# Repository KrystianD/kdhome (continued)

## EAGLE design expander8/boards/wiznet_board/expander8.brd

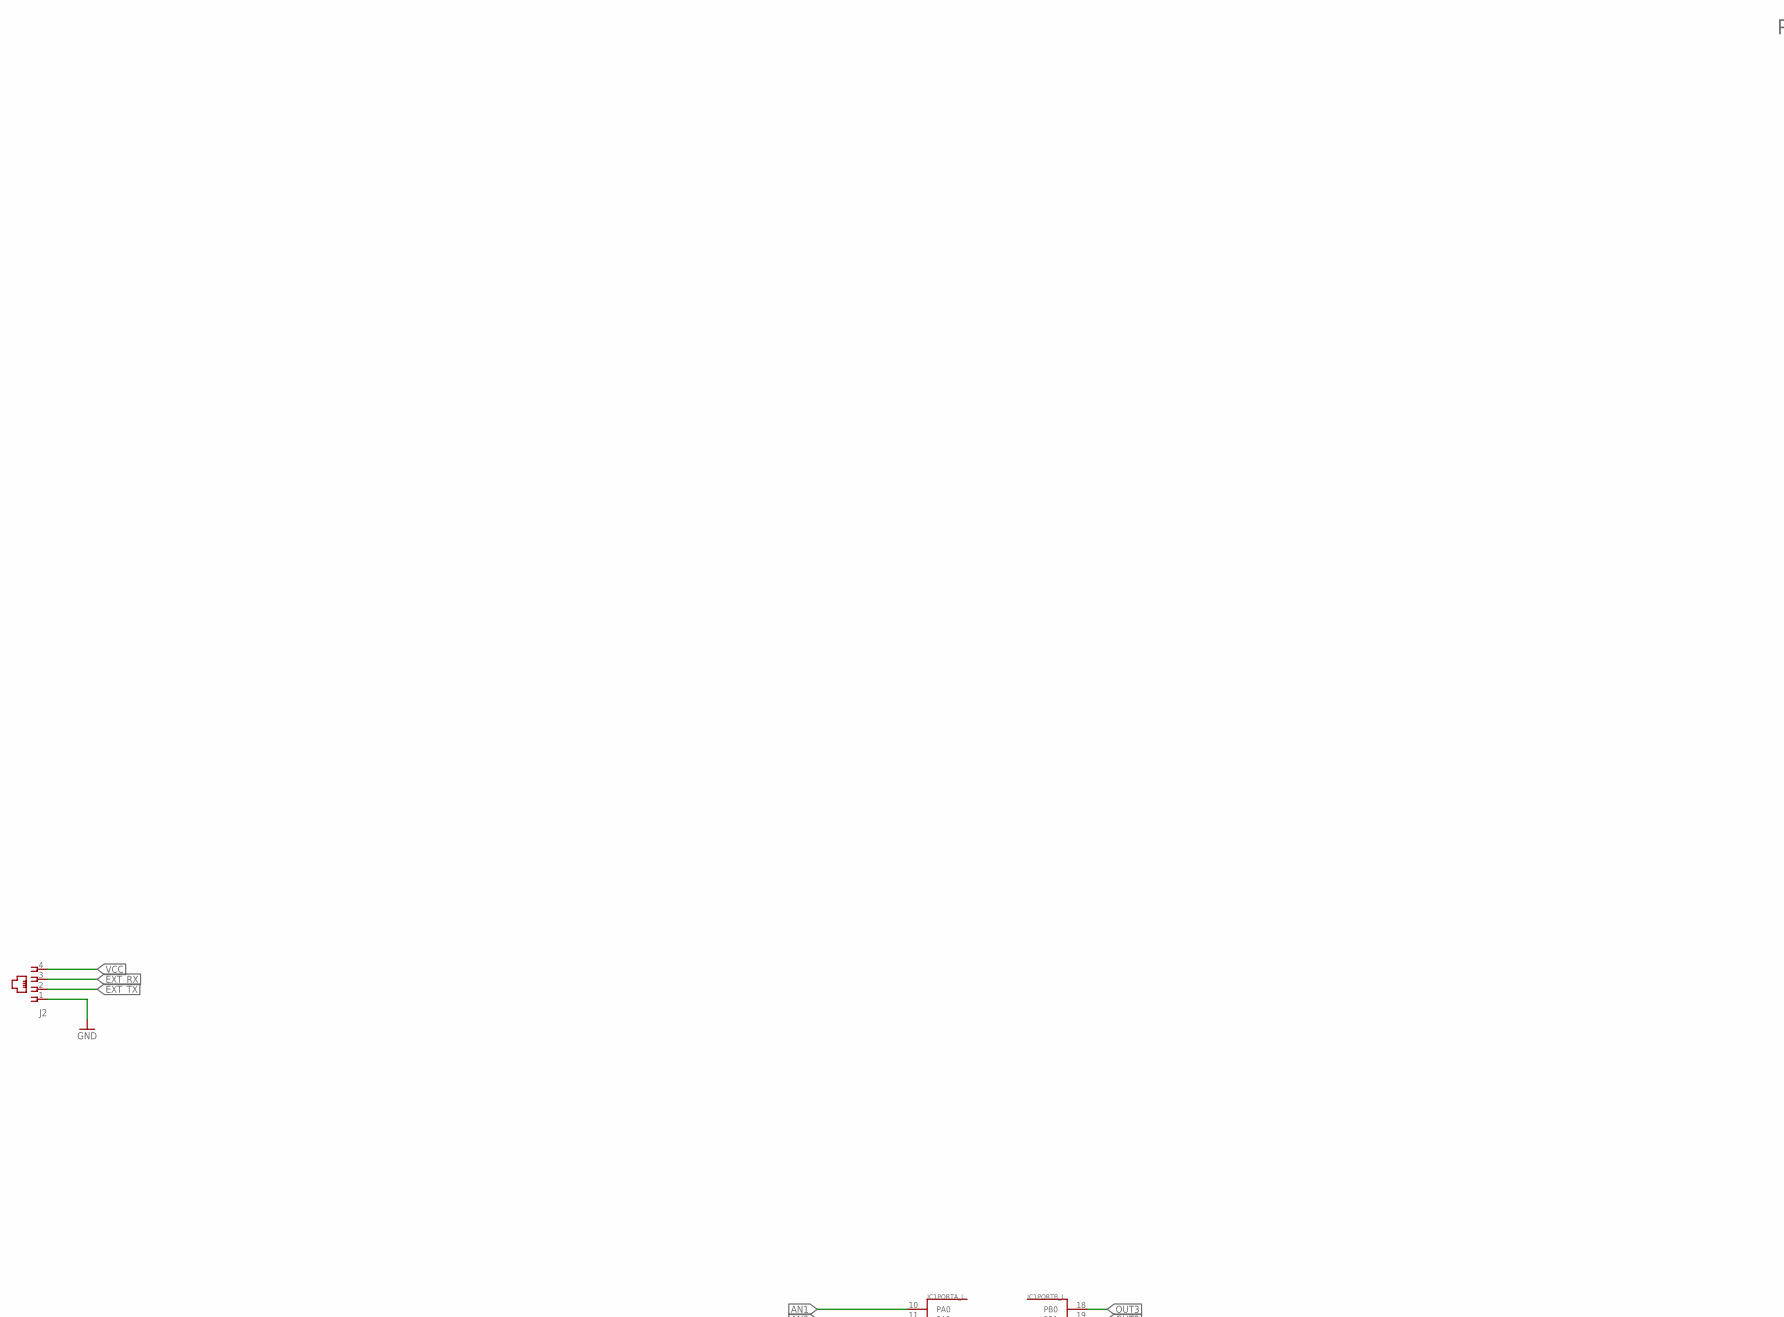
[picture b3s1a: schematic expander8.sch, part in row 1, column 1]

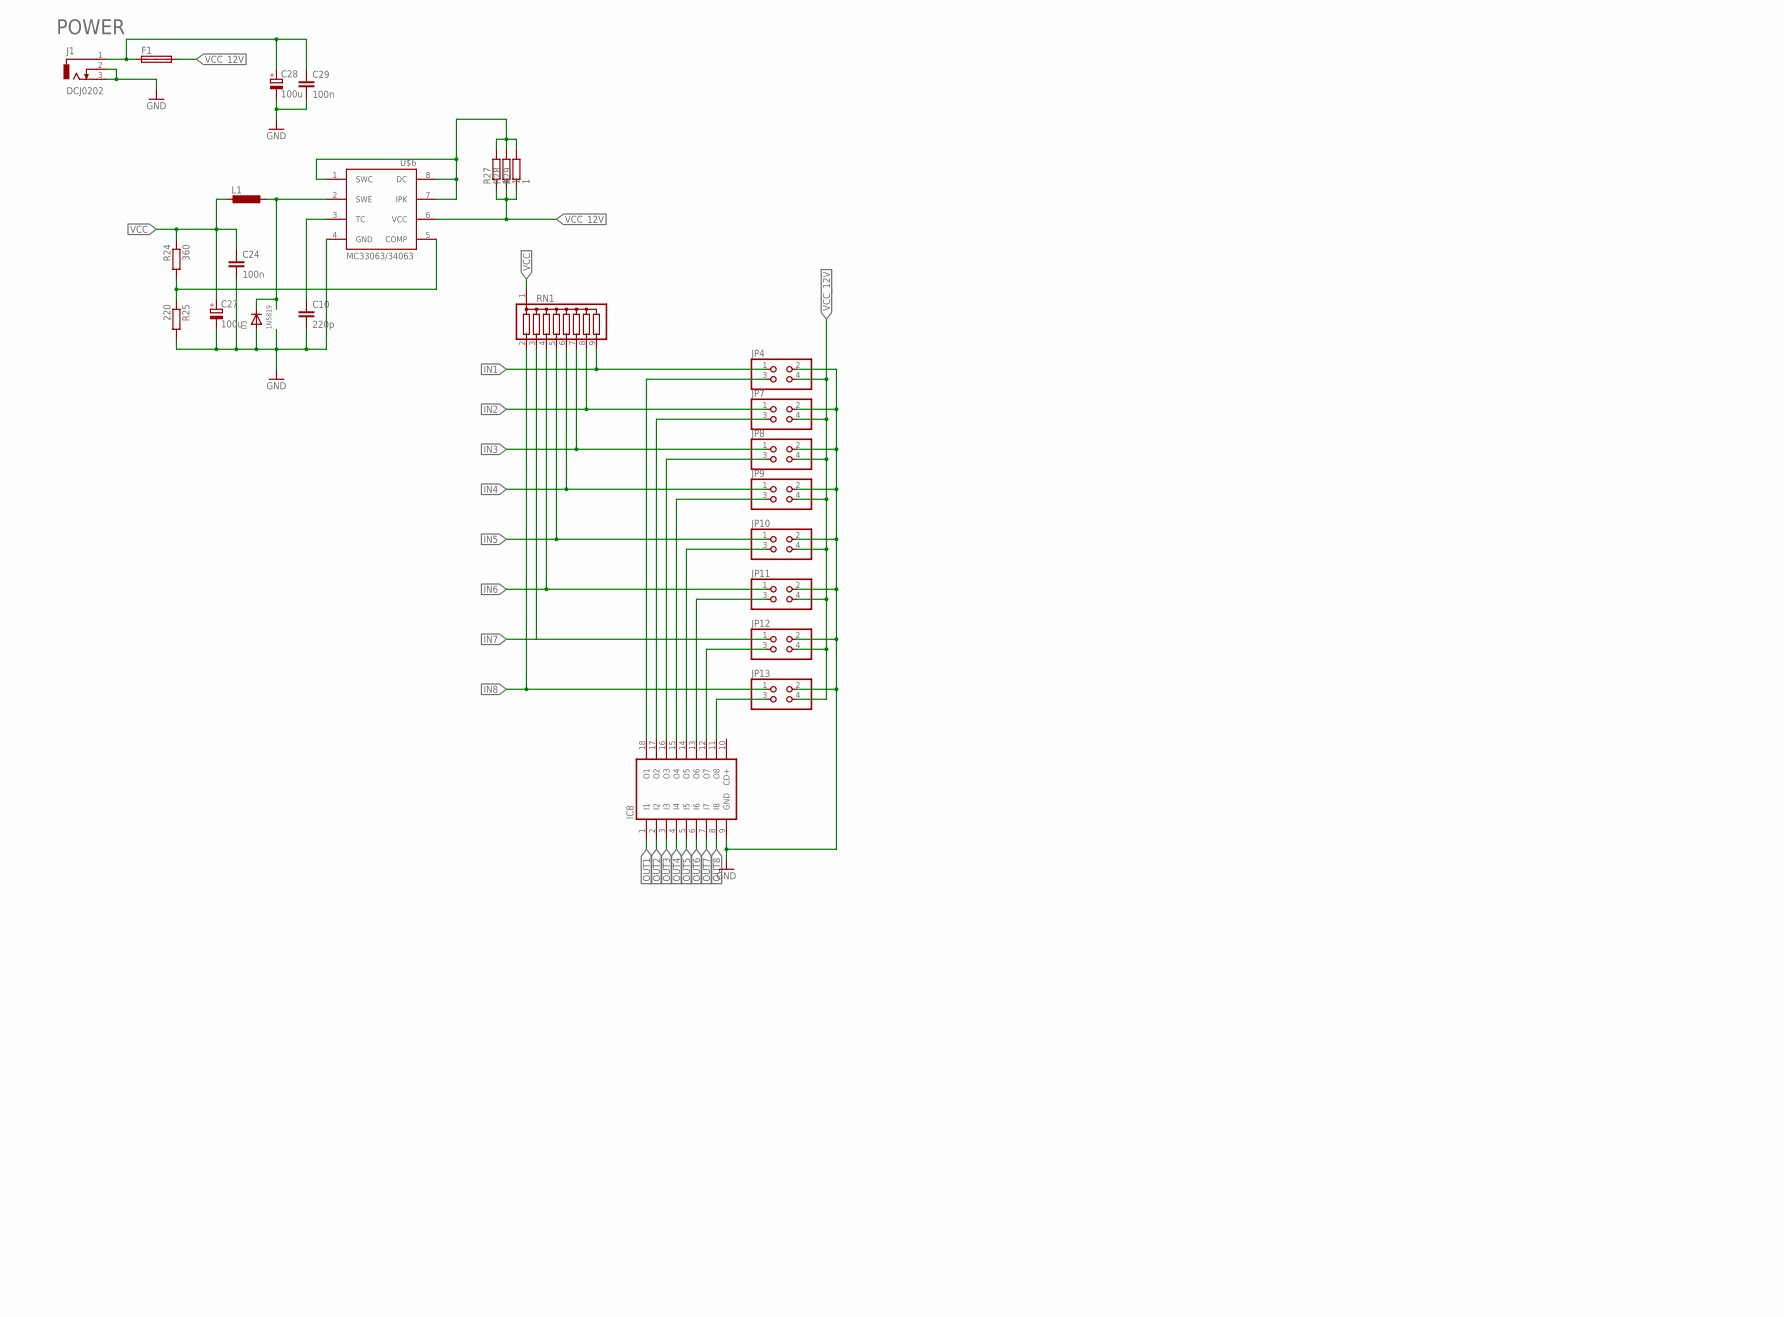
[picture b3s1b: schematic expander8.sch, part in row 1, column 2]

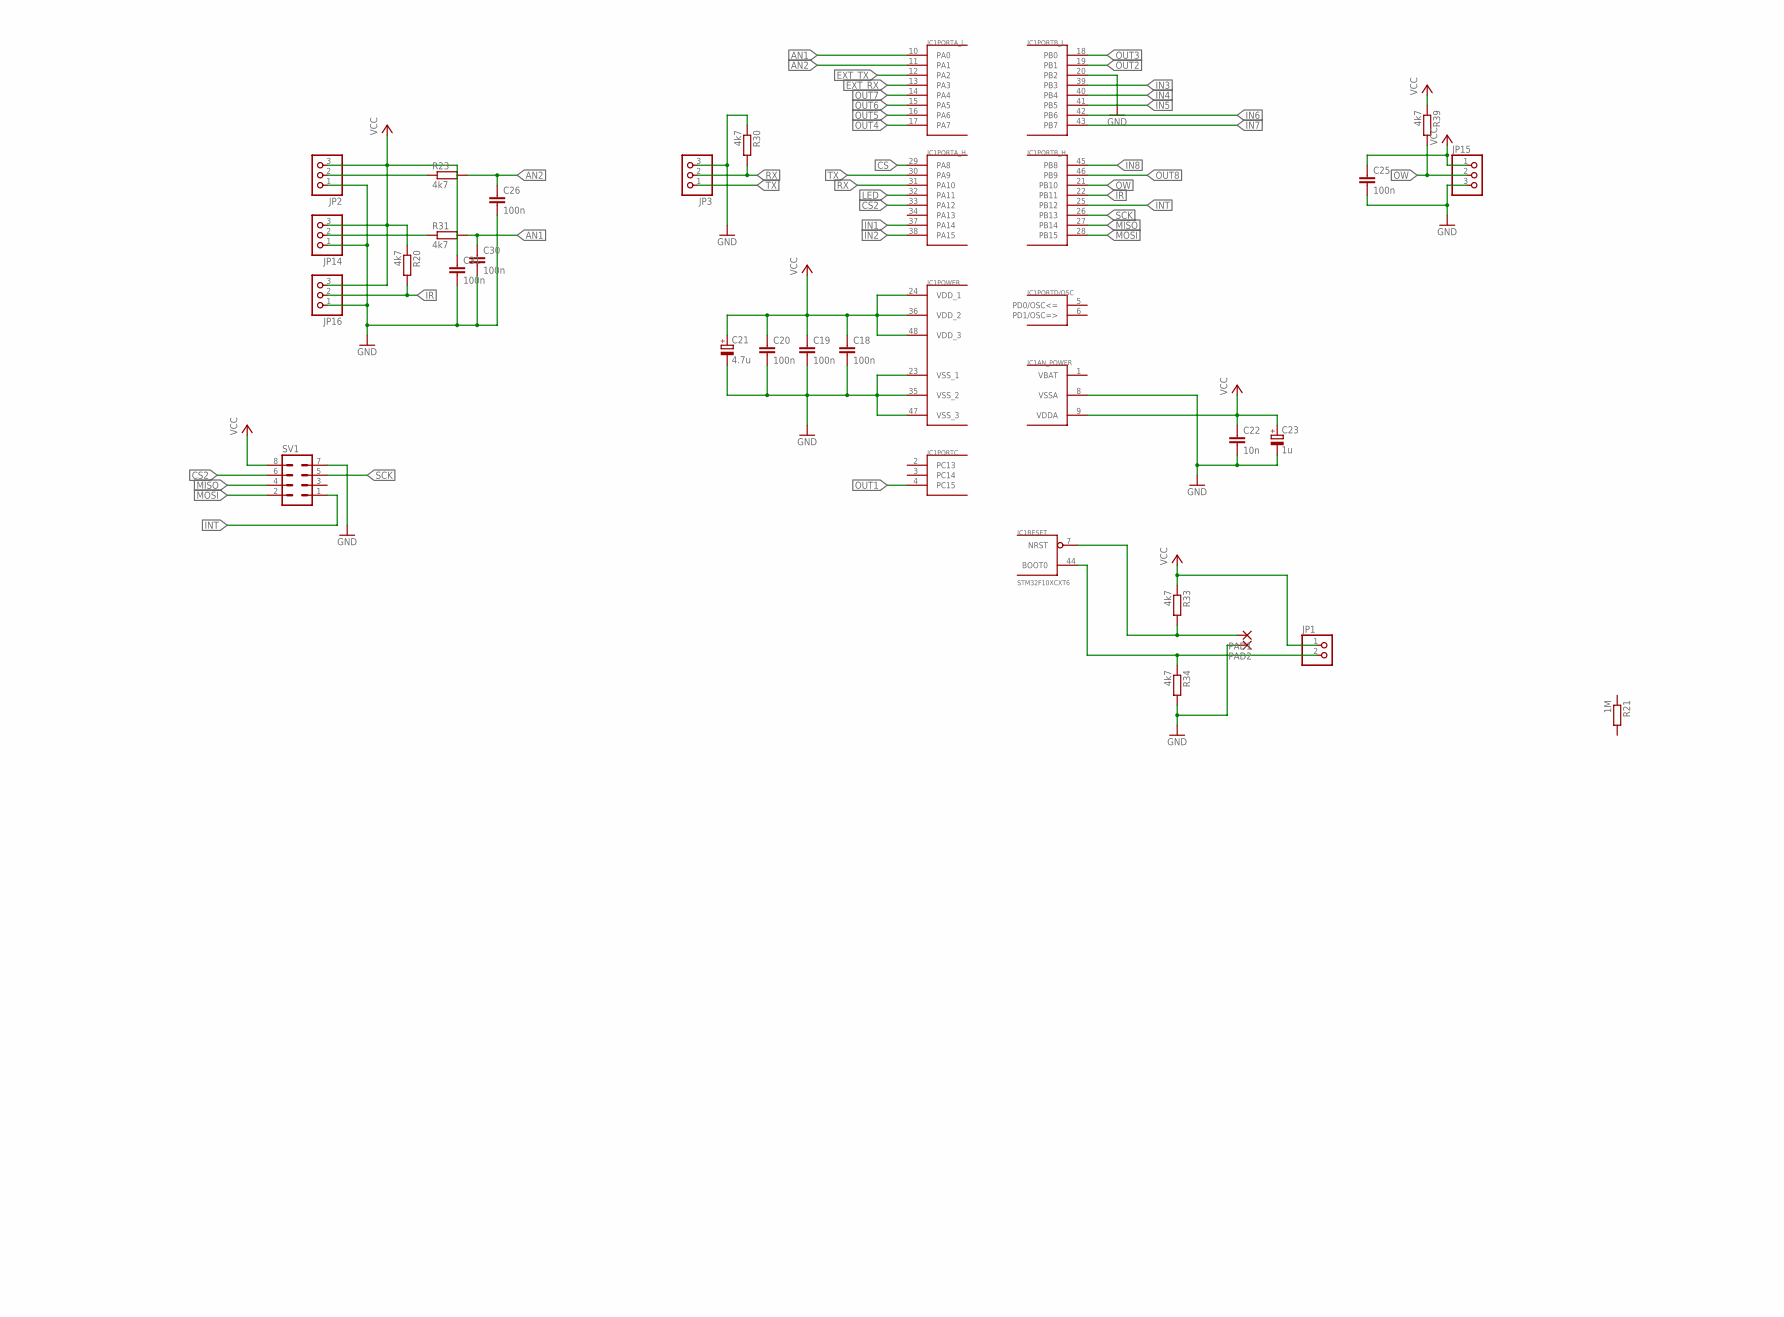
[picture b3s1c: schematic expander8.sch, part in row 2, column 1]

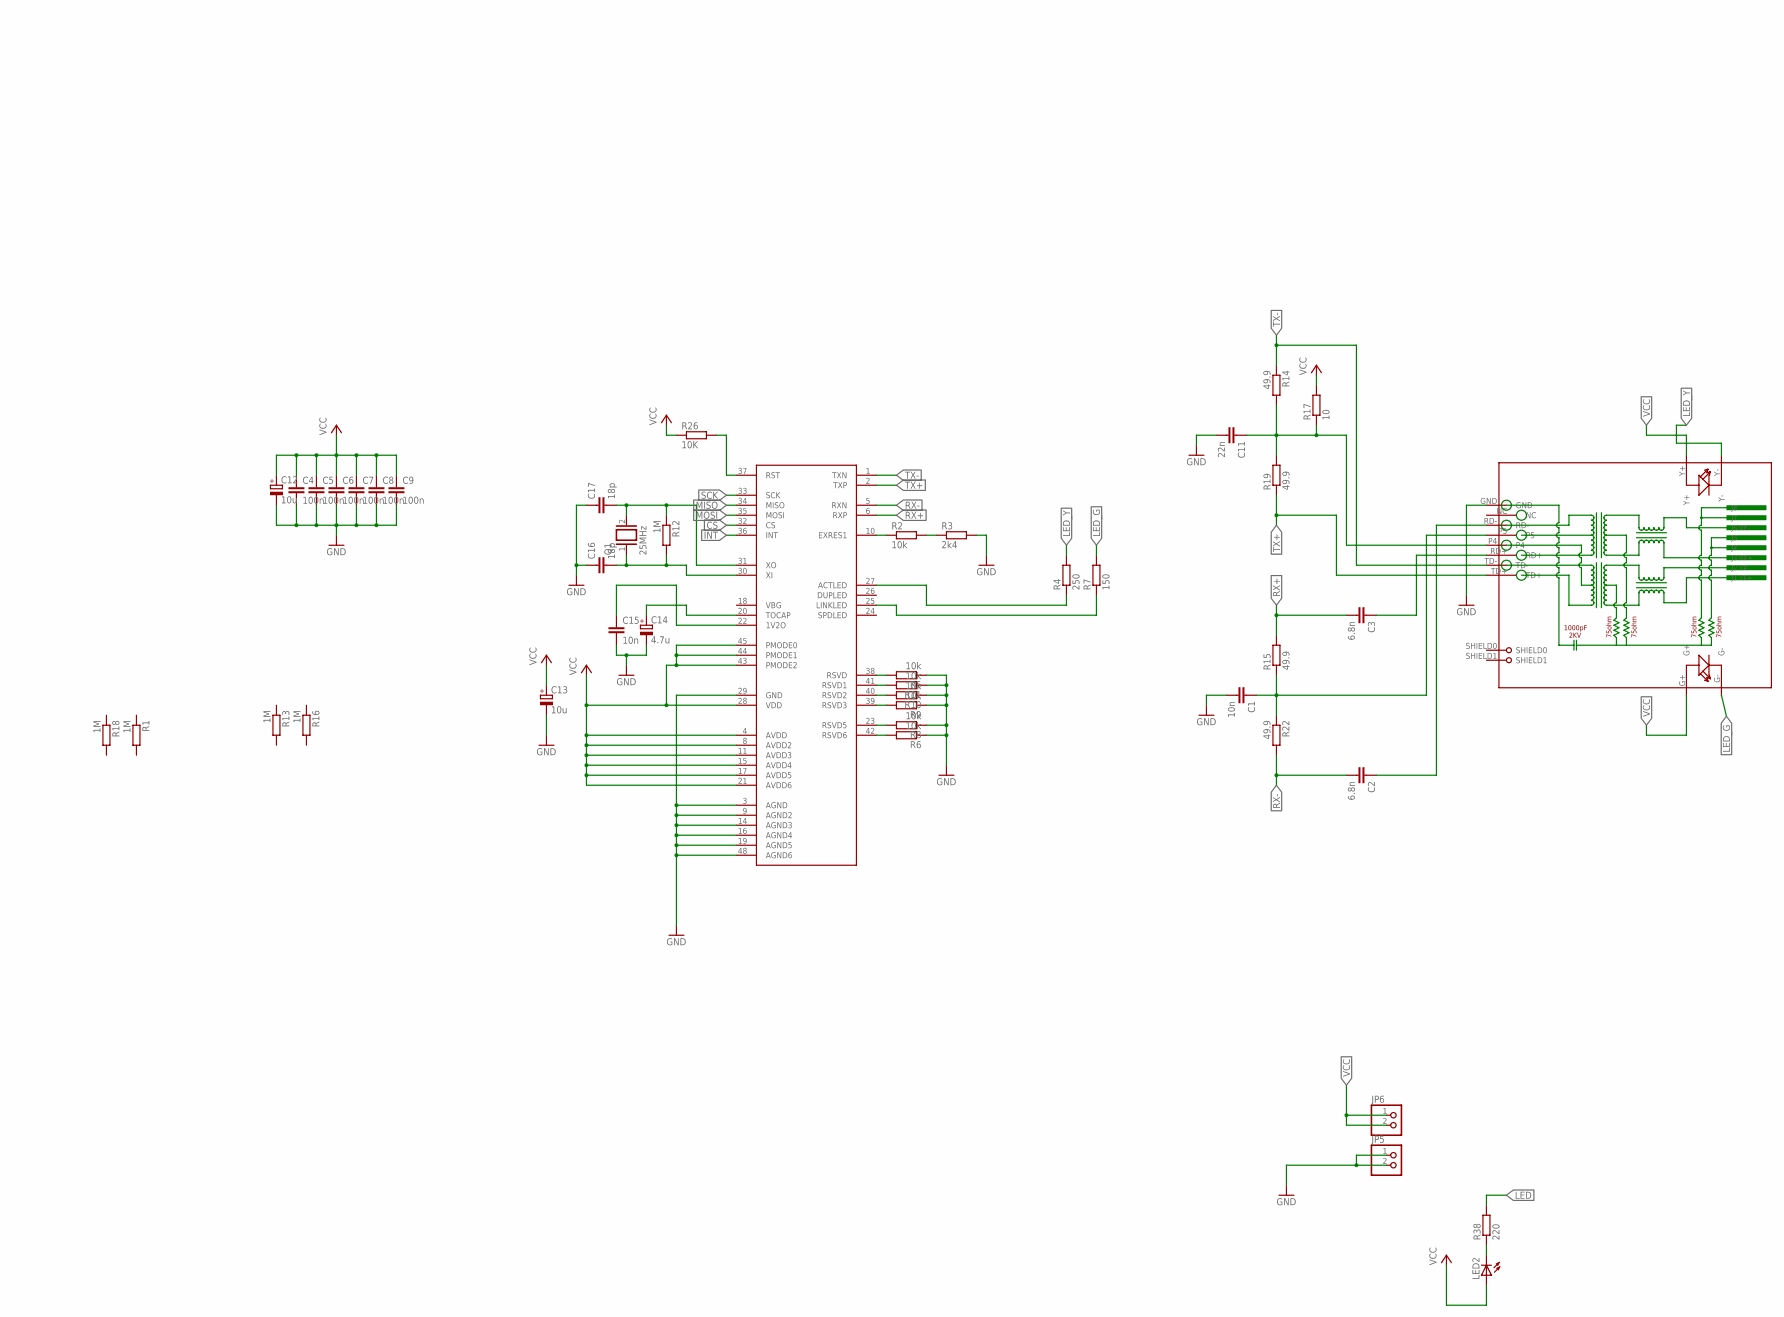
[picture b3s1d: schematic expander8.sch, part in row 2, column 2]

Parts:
C1, C22: 10n; C0805
C2, C3: 6.8n; C0805
C4, C5, C6, C7, C8, C9, C18, C19, C20, C24, C26, C29, C31: 100n; C0805
C10: 220p; C0805
C11: 22n; C0805
C12, C13: 10u; E2,5-5
C14, C21: 4.7u; E2,5-5
C15: 10n; C1206
C16, C17: 18p; C0805
C23: 1u; E2,5-5
C25, C30: 100n; C1206
C27, C28: 100u; E2,5-7
D3: 1N5819; SMADIODE
F1: SHK20L
IC1: STM32F10XCXT6; TQFP48
IC8: ULN2803AD; SO18W
J1: DCJ0202
J2: 520250-2
JP1, JP5, JP6: PINHD-1X2; 1X02
JP2, JP3, JP14, JP15, JP16: PINHD-1X3; 1X03
JP4, JP7, JP8, JP9, JP10, JP11, JP12, JP13: PINHD-2X2/90; 2X02/90
L1: L-EU0207/2V; 0207/2V
LED2: LEDCHIPLED_0805; CHIPLED_0805
PAD1, PAD2: SMD2; SMD1,27-2,54
Q1: 25MHz; QS
R1, R13, R16, R18, R21: 1M; R1206
R2, R8: 10k; R0805
R3: 2k4; R0805
R4: 250; R1206
R5, R6, R9, R10, R11: 10k; R0603
R7: 150; R1206
R12: 1M; R0805
R14, R22: 49.9; R0805
R15, R19: 49.9; R1206
R17: 10; R0805
R20, R23, R31, R33, R39: 4k7; R0805
R24: 360; M1206
R25: 220; M1206
R26: 10K; R0805
R27, R28, R29: 1; R1206
R30, R34: 4k7; R1206
R38: 220; R0805
RJ1: HR911105A
RN1: G08R; SIL9
SV1: MA04-2
U$1: W5500; TQFP48
U$6: MC33063/MC34063D; SO08

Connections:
AN1: C30.1, IC1.10 (PA0), R31.2
AN2: C26.1, IC1.11 (PA1), R23.2
COMP: R24.2, R25.1, U$6.5 (COMP)
CS: IC1.29 (PA8), U$1.32 (CS)
CS2: IC1.33 (PA12), SV1.6
EXT_RX: IC1.13 (PA3), J2.3
EXT_TX: IC1.12 (PA2), J2.2
GND: C1.2, C4.2, C5.2, C6.2, C7.2, C8.2, C9.2, C10.2, C11.2, C12.-, C13.-, C14.-, C15.2, C16.1, C17.1, C18.2, C19.2, C20.2, C21.-, C22.2, C23.-, C24.2, C25.2, C26.2, C27.-, C28.-, C29.2, C30.2, C31.2, D3.A, IC1.8 (VSSA), IC1.20 (PB2), IC1.23 (VSS_1), IC1.35 (VSS_2), IC1.47 (VSS_3), IC8.9 (GND), J1.2, J1.3, J2.1, JP2.1, JP3.3, JP4.2, JP5.1, JP5.2, JP7.2, JP8.2, JP9.2, JP10.2, JP11.2, JP12.2, JP13.2, JP14.1, JP15.3, JP16.1, PAD2.1, R3.2, R5.1, R6.1, R8.1, R9.1, R10.1, R11.1, R25.2, R30.1, R34.2, RJ1.GND, SV1.7, U$1.3 (AGND), U$1.9 (AGND2), U$1.14 (AGND3), U$1.16 (AGND4), U$1.19 (AGND5), U$1.29 (GND), U$1.48 (AGND6), U$6.4 (GND)
IN1: IC1.37 (PA14), JP4.1, RN1.9
IN2: IC1.38 (PA15), JP7.1, RN1.8
IN3: IC1.39 (PB3), JP8.1, RN1.7
IN4: IC1.40 (PB4), JP9.1, RN1.6
IN5: IC1.41 (PB5), JP10.1, RN1.5
IN6: IC1.42 (PB6), JP11.1, RN1.4
IN7: IC1.43 (PB7), JP12.1, RN1.3
IN8: IC1.45 (PB8), JP13.1, RN1.2
INT: IC1.25 (PB12), SV1.1, U$1.36 (INT)
IPK: R27.2, R28.2, R29.2, U$6.1 (SWC), U$6.7 (IPK), U$6.8 (DC)
IR: IC1.22 (PB11), JP16.2, R20.2
LED: IC1.32 (PA11), R38.2
LED_G: R7.2, RJ1.G-
LED_Y: R4.2, RJ1.Y-
MISO: IC1.27 (PB14), SV1.4, U$1.34 (MISO)
MOSI: IC1.28 (PB15), SV1.2, U$1.35 (MOSI)
unnamed: C3.1, RJ1.RD+
unnamed: C2.1, RJ1.RD-
unnamed: IC8.18 (O1), JP4.3
unnamed: IC8.17 (O2), JP7.3
unnamed: R2.1, U$1.10 (EXRES1)
unnamed: R2.2, R3.1
unnamed: C15.1, U$1.22 (1V2O)
unnamed: C14.+, U$1.20 (TOCAP)
unnamed: C17.2, Q1.2, R12.1, U$1.31 (XO)
unnamed: IC8.16 (O3), JP8.3
unnamed: R5.2, U$1.38 (RSVD)
unnamed: IC8.15 (O4), JP9.3
unnamed: R4.1, U$1.27 (ACTLED)
unnamed: R11.2, U$1.41 (RSVD1)
unnamed: R10.2, U$1.40 (RSVD2)
unnamed: R7.1, U$1.25 (LINKLED)
unnamed: R9.2, U$1.39 (RSVD3)
unnamed: R8.2, U$1.23 (RSVD5)
unnamed: R6.2, U$1.42 (RSVD6)
unnamed: C16.2, Q1.1, R12.2, U$1.30 (XI)
unnamed: IC8.14 (O5), JP10.3
unnamed: IC8.13 (O6), JP11.3
unnamed: IC8.12 (O7), JP12.3
unnamed: LED2.C, R38.1
unnamed: R26.2, U$1.37 (RST)
unnamed: IC8.11 (O8), JP13.3
unnamed: JP2.2, R23.1
unnamed: JP14.2, R31.1
unnamed: C11.1, R14.2, R17.1, R19.2, RJ1.P4
unnamed: D3.C, L1.1, U$6.2 (SWE)
unnamed: C10.1, U$6.3 (TC)
unnamed: C28.+, C29.1, F1.1A, J1.1
unnamed: IC1.44 (BOOT0), JP1.2, R34.1
unnamed: C1.1, R15.1, R22.1, RJ1.P5
OUT1: IC1.4 (PC15), IC8.1 (I1)
OUT2: IC1.19 (PB1), IC8.2 (I2)
OUT3: IC1.18 (PB0), IC8.3 (I3)
OUT4: IC1.17 (PA7), IC8.4 (I4)
OUT5: IC1.16 (PA6), IC8.5 (I5)
OUT6: IC1.15 (PA5), IC8.6 (I6)
OUT7: IC1.14 (PA4), IC8.7 (I7)
OUT8: IC1.46 (PB9), IC8.8 (I8)
OW: IC1.21 (PB10), JP15.2, R39.2
RST1: IC1.7 (NRST), PAD1.1, R33.2
RX: IC1.31 (PA10), JP3.2, R30.2
RX+: C3.2, R15.2, U$1.6 (RXP)
RX-: C2.2, R22.2, U$1.5 (RXN)
SCK: IC1.26 (PB13), SV1.5, U$1.33 (SCK)
TX: IC1.30 (PA9), JP3.1
TX+: R19.1, RJ1.TD+, U$1.2 (TXP)
TX-: R14.1, RJ1.TD-, U$1.1 (TXN)
VBAT: IC1.1 (VBAT)
VCC: C4.1, C5.1, C6.1, C7.1, C8.1, C9.1, C12.+, C13.+, C18.1, C19.1, C20.1, C21.+, C22.1, C23.+, C24.1, C25.1, C27.+, C31.1, IC1.9 (VDDA), IC1.24 (VDD_1), IC1.36 (VDD_2), IC1.48 (VDD_3), J2.4, JP1.1, JP2.3, JP6.1, JP6.2, JP14.3, JP15.1, JP16.3, L1.2, LED2.A, R17.2, R20.1, R24.1, R26.1, R33.1, R39.1, RJ1.G+, RJ1.Y+, RN1.1, SV1.8, U$1.4 (AVDD), U$1.8 (AVDD2), U$1.11 (AVDD3), U$1.15 (AVDD4), U$1.17 (AVDD5), U$1.21 (AVDD6), U$1.28 (VDD), U$1.43 (PMODE2), U$1.44 (PMODE1), U$1.45 (PMODE0)
VCC_12V: F1.2A, JP4.4, JP7.4, JP8.4, JP9.4, JP10.4, JP11.4, JP12.4, JP13.4, R27.1, R28.1, R29.1, U$6.6 (VCC)

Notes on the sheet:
POWER

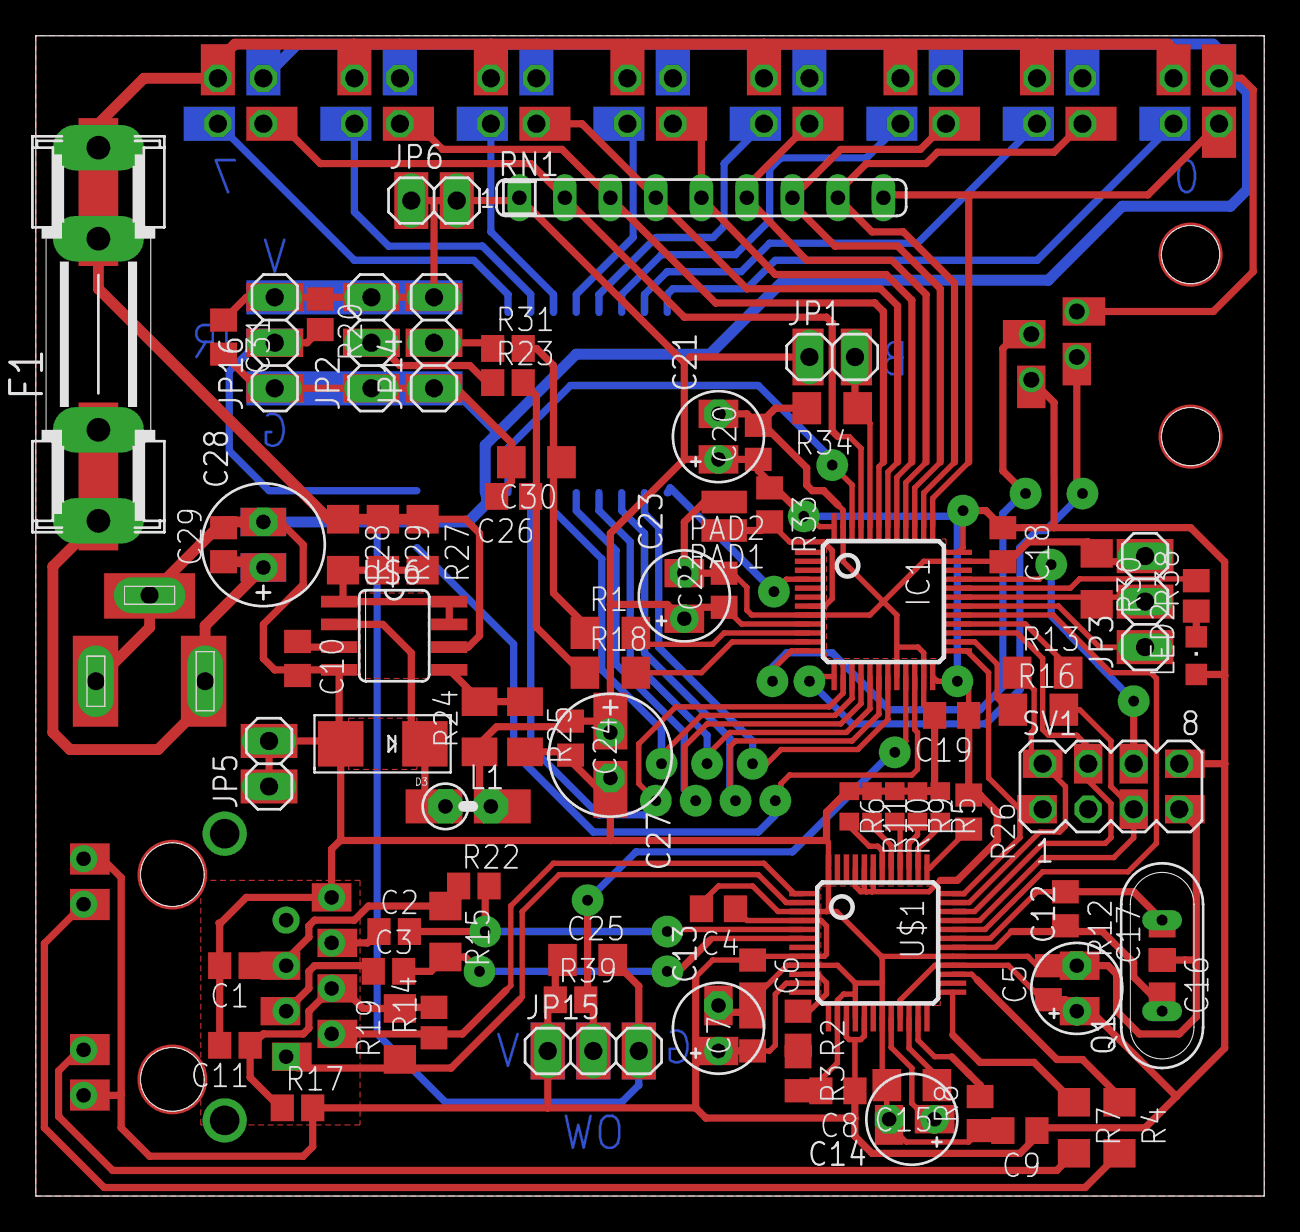
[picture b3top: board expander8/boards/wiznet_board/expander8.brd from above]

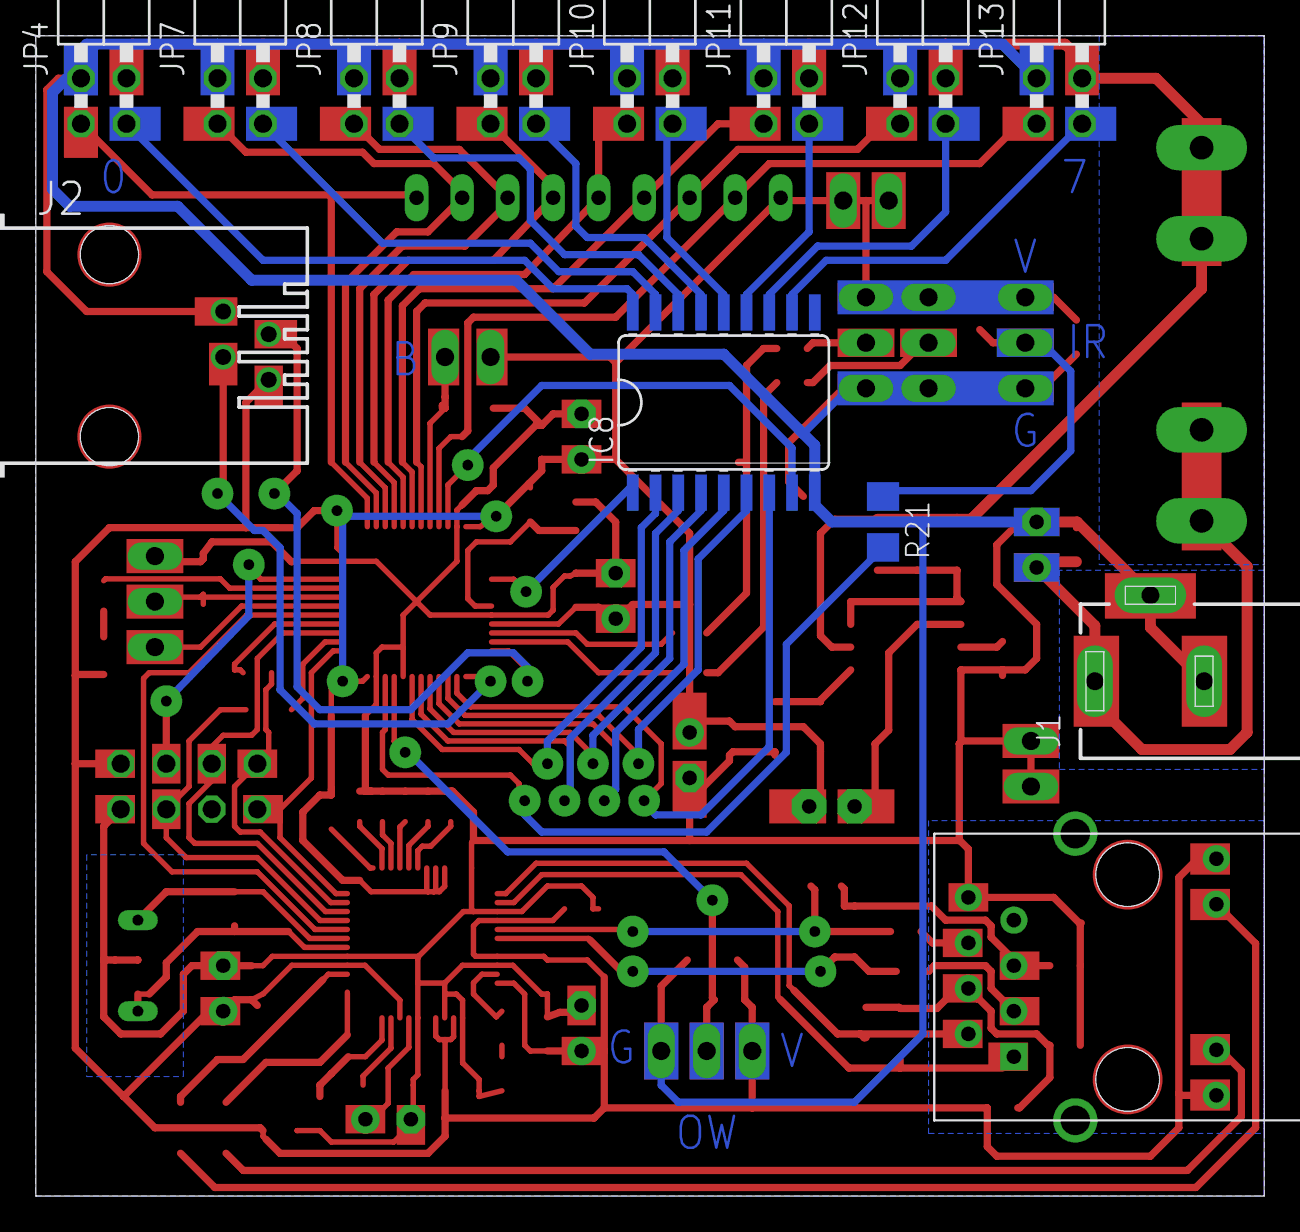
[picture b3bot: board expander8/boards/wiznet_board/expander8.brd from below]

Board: 2 copper layers, 68.6 x 64.8 mm, 98 parts (13 on the bottom side), 77 nets.

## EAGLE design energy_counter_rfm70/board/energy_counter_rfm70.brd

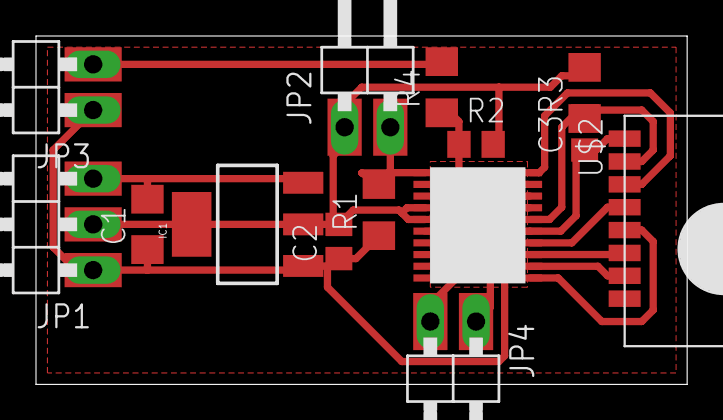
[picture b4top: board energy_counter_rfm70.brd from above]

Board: 2 copper layers, 36.2 x 19.4 mm, 14 parts (0 on the bottom side), 12 nets.

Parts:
C1: C1206
C2, C3: C0805
IC1: SOT223
JP1: 1X03/90
JP2, JP3, JP4: 1X02/90
R1, R3, R4: R1206
R2: R0805
U$1: STM32F0; TSSOP20
U$2: RFM70-DSMD; RFM70-SMD

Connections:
CE: U$1.PA14, U$2.CE
CSN: U$1.PB1, U$2.CSN
GND: C1.1, C2.1, C3.1, IC1.1, JP1.1, JP3.1, R1.1, U$1.VSS, U$2.GND
MISO: U$1.PA6, U$2.MISO
MOSI: U$1.PA7, U$2.MOSI
unnamed: C1.2, IC1.3, JP1.3
unnamed: JP2.2, R1.2, U$1.BOOT0
unnamed: JP3.2, R2.1, U$1.PA0
RX: JP4.2, U$1.PA10
SCK: U$1.PA5, U$2.SCK
TX: JP4.1, U$1.PA9
VCC: C2.2, C3.2, IC1.2, JP1.2, JP2.1, R2.2, U$1.NRST, U$1.VDD, U$1.VDDA, U$2.VDD

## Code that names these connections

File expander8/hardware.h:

#ifndef __HARDWARE_H__
#define __HARDWARE_H__

#define UART_TX GPIOA,9

#define LED GPIOA,11
#define OW GPIOB,10
#define IR GPIOB,11 // TIM2_CH4

#define IN1 GPIOA,14
#define IN2 GPIOA,15
#define IN3 GPIOB,3
#define IN4 GPIOB,4
#define IN5 GPIOB,5
#define IN6 GPIOB,6
#define IN7 GPIOB,7
#define IN8 GPIOB,8

#if VERSION == 1
#  define OUT1 GPIOB,11
#  define OUT2 GPIOB,1
#  define OUT3 GPIOB,0
#  define OUT4 GPIOA,7
#  define OUT5 GPIOA,6
#  define OUT6 GPIOA,5
#  define OUT7 GPIOA,4
#  define OUT8 GPIOB,9
#elif VERSION == 2
#  define OUT1 GPIOC,15
#  define OUT2 GPIOB,1
#  define OUT3 GPIOB,0
#  define OUT4 GPIOA,7
#  define OUT5 GPIOA,6
#  define OUT6 GPIOA,5
#  define OUT7 GPIOA,4
#  define OUT8 GPIOB,9
#endif

#ifdef ETHERNET
#  define SCK GPIOB,13
#  define MISO GPIOB,14
#  define MOSI GPIOB,15
#  define W_CS GPIOA,8
#  define INT_ETH GPIOB,12
#endif

#ifdef ESP
#  define ESP_TX    GPIOA,2
#  define ESP_RX    GPIOA,3
#  define ESP_RST   GPIOA,11
#  define ESP_CH_PD GPIOA,12
#endif

#endif

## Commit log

2014-01-17 cleaning
2014-01-17 path fixed
2014-01-17 added gitignore
2014-01-17 makefile fixed
2014-01-18 server: fixed connection lost tracking
2014-01-19 server: added some logs server: fixed registratoin server: fixed curl cleaning server: remove connection param from lua bindings server: added buffer protections
2014-01-21 server: changed packet loss delay cleaning
2014-01-21 server: added srand cleaning
2014-01-22 added expander16 project
2014-01-22 server: prevent disconnecting on packetId wrap
2014-01-25 server: added getTime() function to script
2014-01-25 expander: moved every provider to its own module
2014-01-25 expander: added basic temp interface
2014-01-25 expander: added valid temperature implementation
2014-01-25 expander: fixed temp
2014-01-26 server: implemented temperature provider expander: disabled implicit function declarations
2014-01-26 Security fix
    Removed some testing code
2014-01-26 expander: added stm32-public as submodule expander: fixed hardware config
2014-01-26 expander: stm32-public sync
2014-01-26 expander: added Arduino-IRremote as submodule
2014-02-11 expander: made use of temperature provider
2014-02-17 server: added json module
2014-02-17 expander: disabled auto resetting
2014-03-14 server: added outputs persistent storage
2014-03-17 server: started usb support
2014-03-30 uc: moved common files to another directory added expander8_avr_usb project
2014-03-30 .gitignore
2014-03-30 added libconfig to clean
2014-03-30 fixed Makefile
2014-03-30 server: added some logs
2014-03-30 expander: added missing file to lwip library
2014-03-31 server: fixed storage engine server: saving state of changed output only
2014-04-11 fixed listening on all addresses
2014-08-14 server: added passing HTTP client real ip to script
2014-10-07 added expander8 project moved providers to separate directory
2014-10-07 removed ir-remote submodule
2014-10-07 moved 3rd dir
2014-10-07 readded ir-remote submodule
2014-10-07 added kdutils project
2014-10-07 replaced dynamic buffer with static one expander8: adjusted input, output and ir provider
2014-10-08 started moving to zeromq
2014-10-08 server: added processing and sending zmq events py: added library for processing zmq events
2014-10-08 expander8: fixed temp provider
2014-10-08 server: removed lua code server: added IO naming
2014-10-09 server: split init into init and reload functions server: fixed StorageEngine server: added device unloading on reload py: added simple intervals handling
2014-10-10 server: introduced blocking event loop
2014-10-10 expander8: removed unused files
2014-10-27 expander8: fixed compilation server: removed unused code
2014-10-31 expander8: added 1wire sensors search
2014-11-03 server: moved shared IO nums to dev-num pairs server: changed providers registering method
2014-11-04 server: added names maps clearing
2014-11-16 added energy monitor projects (energy_rf and rf_receiver)
2014-11-18 rf_receiver: better logging
2014-12-16 server: made use of IR provider server: changed format of IR codes to hex server: fixed bug of not deleting providers on device disconnect event
2014-12-16 rf_receiver: more testing
2014-12-16 added UdpSocket class
2014-12-16 removed myprintf dependencies from providers
2015-01-05 server: added port setting
2015-01-05 kdutils update
2015-01-06 exp8: small fixes
2015-01-06 exp8-esp: added custom esp firmware
2015-01-06 added expanders boards and schematics
2015-01-06 dirs renamed
2015-01-06 merged esp and wiznet expanders into one project
2015-01-06 temporary removed submodules
2015-01-06 fixed submodules
2015-01-06 expander16: adjusted for new stm32-utils
2015-01-06 removed unused files code cleanup
2015-01-06 providers: added c++ support providers: added defines for disabling providers providers: presence notification moved into providers module server: added port to EthernetDevice
2015-01-06 added endpoint_template
2015-01-06 added listing of providers callbacks added missing Makefile
2015-01-07 removed unused lua files
2015-01-09 providers: added counter provider
2015-01-13 server: restored persistent outputs functionality
2015-01-13 added base classes and files for Counter provider
2015-01-13 fixed makefile in this branch
2015-01-13 added config.cfg for KD build system
2015-01-13 fixed config.cfg
2015-01-13 added CounterProvider.cpp to config.cfg
2015-01-13 fixed .gitignore files
2015-01-13 project renamed
2015-02-17 added ESP GPIO2 connection
2015-02-17 added publishing Counter notifications
2015-02-17 providers: fixed repeating code processing in IR provider
2015-02-17 providers: fixed input state getter
2015-02-17 added counter example to endpoint_template
2015-02-17 server: added counter names
2015-02-17 replaced energy_counter endpoint project
2015-02-17 added kdhome python library
2015-02-24 endpoint_energy: added auto reopening device
2015-02-24 server: added custom log file cli option
2015-02-24 script: added hasTimeout/Interval and removeTimeout/Interval functions
2015-02-24 boards: added vcc polygon under dcdc
2015-03-05 server: changed providers class names
2015-03-05 server: added IO layer to persist input/output states across endpoint resets
2015-03-05 added struct containing IO info
2015-03-05 bug fixed in counter provider
2015-03-05 removed Program class and added user logger
2015-03-05 server: made use of user log
2015-03-07 server: fixed timer setting, added log function
2015-11-07 ported expander16 to new protocol
2016-03-23 fixed building
